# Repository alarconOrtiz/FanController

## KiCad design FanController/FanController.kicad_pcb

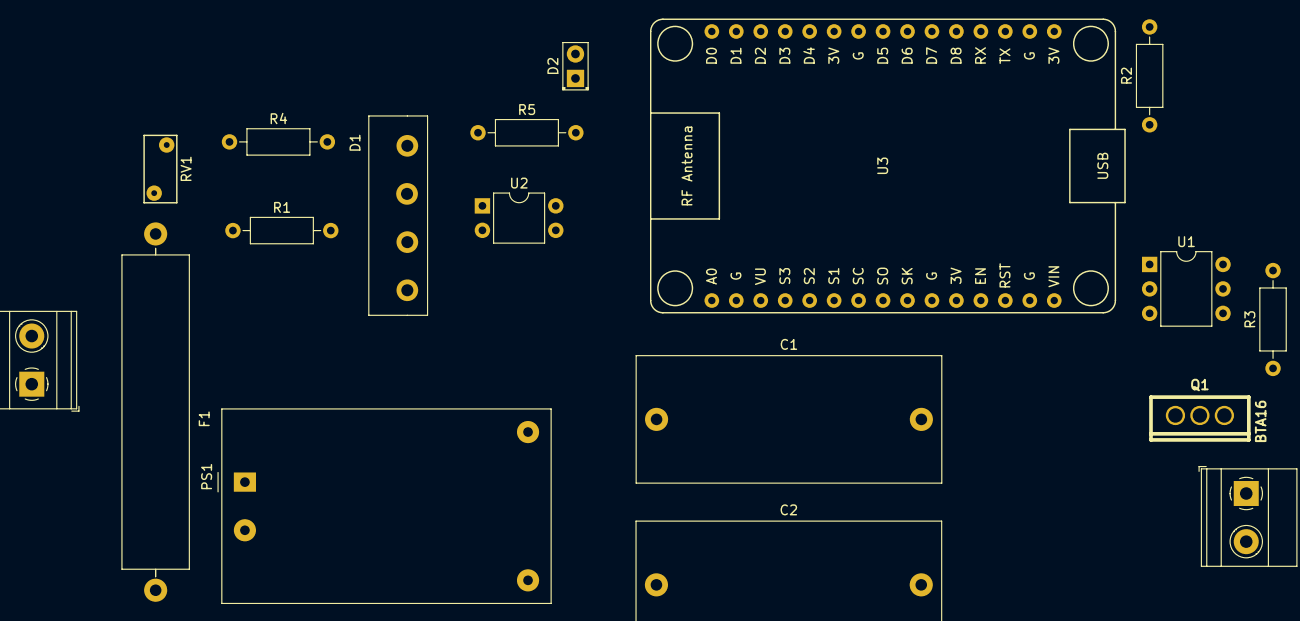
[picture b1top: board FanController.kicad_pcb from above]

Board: 2 copper layers, 18 parts (0 on the bottom side), 18 nets, no tracks yet.

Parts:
C1: 10uf; C_Rect_L31.5mm_W13.0mm_P27.50mm_MKS4
C2: 22uf; C_Rect_L31.5mm_W13.0mm_P27.50mm_MKS4
D1: KBL10; kbl10
D2: LED; LED_D2.0mm_W4.8mm_H2.5mm_FlatTop
F1: Fuse; Fuse_SunFuse-6HP
J1: AC; TerminalBlock_Phoenix_MKDS-1,5-2_1x02_P5.00mm_Horizontal
J2: AC Out; TerminalBlock_Phoenix_MKDS-1,5-2_1x02_P5.00mm_Horizontal
PS1: HLK-PM03; Converter_ACDC_HiLink_HLK-PMxx
Q1: BTA16; TO-220AB
R1, R4: 47K; R_Axial_DIN0207_L6.3mm_D2.5mm_P10.16mm_Horizontal
R2: 100; R_Axial_DIN0207_L6.3mm_D2.5mm_P10.16mm_Horizontal
R3: 200; R_Axial_DIN0207_L6.3mm_D2.5mm_P10.16mm_Horizontal
R5: 1K; R_Axial_DIN0207_L6.3mm_D2.5mm_P10.16mm_Horizontal
RV1: Varistor; RV_Disc_D7mm_W3.4mm_P5mm
U1: MOC3020; DIP-6_W7.62mm
U2: EL817; DIP-4_W7.62mm
U3: NodeMCU1.0(ESP-12E); NodeMCU1.0(12-E)

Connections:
3V3: U3.11, U3.16, U3.25
220AC: F1.2, PS1.1, Q1.2, R1.1, R3.1, RV1.1
+3V3: C1.1, C2.1, PS1.4, U3.14
ADC: R5.1, U2.4, U3.1
Fase_out: J2.1, Q1.1
GND: C1.2, C2.2, PS1.3, U3.15
GND_3V3: D2.1, R5.2, U1.2, U3.10, U3.17, U3.24
unnamed: D1.1, U2.1
unnamed: D1.2, R4.2
unnamed: D1.3, R1.2
unnamed: D1.4, U2.2
unnamed: D2.2, U3.29
unnamed: F1.1, J1.1
unnamed: Q1.3, U1.4
unnamed: R2.1, U1.1
unnamed: R3.2, U1.6
Neutro: J1.2, J2.2, PS1.2, R4.1, RV1.2
fase_flag: R2.2, U3.30

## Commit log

2020-08-05 added readme file
2020-08-06 added in schematic ASDC suplier for ESP12E.
2020-08-07 added capacitor network at the output of ACDC
2020-08-08 renamed conector J1 adn J2
2020-08-08 placed components in a preliminary location
